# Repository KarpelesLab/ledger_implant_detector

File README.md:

# Ledger Implant Detector

> **⚠️ STATUS: CONCEPT — NOT YET BUILT OR VALIDATED (rev 0.1)**
>
> This hardware has **not been fabricated or tested yet**. The schematic,
> layout and detection method are a first-pass concept and will almost
> certainly need errata. Do not rely on this device to declare a wallet
> "clean" until the design has been built, characterised against known-good
> and known-tampered devices, and this banner has been removed.

A small hand-held tool for spotting **extra conductive structures hidden inside
the plastic shell of a hardware wallet** (e.g. a Ledger). The target threat is
a supply-chain implant that adds a cellular (LTE) modem to the device: such
implants need a comparatively large antenna, i.e. a sizeable area of copper
that is not present in a genuine unit.

Everything is on **one board**, powered and programmed over a single USB-C
port. No programmer or debug probe is needed (see
[Programming](#programming-no-tools-needed)).

## How it detects

The tool combines two complementary methods:

### 1. Capacitive electrode array (primary)

Eight 14 × 14 mm copper electrodes on the underside of the head are read by two
TI **FDC2214** 28-bit capacitance-to-digital converters (LC-resonant, EMI
tolerant). Any conductor close to a plate (an antenna trace, a ground plane, a
battery…) increases that plate's capacitance and lowers its resonance
frequency, which the FDC2214 measures with very high resolution.

The detector does **not** recognise an antenna by itself: a genuine wallet
also contains copper (PCB, battery, display, Bluetooth antenna, NFC coil on
newer models). The method is **differential**:

1. Lay a *known-genuine* unit of the same model on the head in a fixed
   orientation (a 3D-printed jig is recommended) and record the 8-channel
   signature (the "reference").
2. Lay the unit under test in the same position and compare.
3. A significant positive deviation localised to one or more electrodes means
   "more conductor here than in the reference" → open the device / investigate.

The array covers 65 × 34 mm, enough for a Nano S Plus / Nano X in a single
placement; Stax / Flex need two or more positions.

### 2. Near-field RF loop at the tip (secondary, needs a VNA)

The nose of the board carries a printed 8 mm H-field loop, fed by a 50 Ω
microstrip that runs back to an **edge SMA connector** next to the USB-C port.
Plug in an inexpensive VNA (NanoVNA / LiteVNA), sweep S11 from roughly
600 MHz to 3 GHz and hover the tip over the wallet. You are looking for
**resonances in the LTE bands** that a genuine unit does not show.

This is complementary to the capacitive method: capacitance tells you *where
there is extra copper*, and the RF sweep hints at *whether that copper is tuned
like an antenna*. Results are again comparative (reference unit vs. unit under
test). The wallet's own ground plane, battery, Bluetooth antenna and NFC coil
all produce responses of their own, and a hidden antenna's resonance shifts
with its surroundings.

A later revision is meant to integrate the RF sweep so no external VNA is
needed. The measurements in [docs/rf_measurements.md](docs/rf_measurements.md)
will decide whether a magnitude-only front end is enough or phase is needed.

## Simulations

[docs/simulation.md](docs/simulation.md) models the real antenna (from photos of
a tampered unit) sandwiched between the shell and the Ledger's own battery.
Summary so far: antenna copper that sticks out beyond the battery's outline is
clearly detectable, above any plausible placement error. Copper lying entirely
within the battery's outline (it is always glued between the shell and the
battery) and electrically floating is not detectable capacitively.
Placement (air gap) dominates the raw signal, so the wallet must be pressed flat
and judged by the *shape* of the 8-channel signature. The RF loop over the
antenna's feed area shows a narrow in-band absorption dip (~0.35 dB, at ~1.8 GHz
in the model) that a plain-copper piece of the same outline does not. That
feature tells an antenna apart from a battery or other metal, and is within
reach of a scalar, VNA-less front end.

The first NanoVNA session on a tampered Nano X
([data/rf/2026-10-18/notes.md](data/rf/2026-10-18/notes.md)) found a clear S21
hump at 820-850 MHz, but only with the probe right over the antenna's feed. To
remove that position dependence there is now a **concept RF fixture kit**
(slot line and open TEM cell, 80 × 80 mm test area, NanoVNA S11/S21), with
JLCPCB files. See [docs/fixtures.md](docs/fixtures.md). In simulation, both
fixtures see a narrow tampering notch at every wallet placement tested.

**First fixture measurements (2026-10-26, one genuine and one tampered Nano X,
[data/rf/2026-10-26/notes.md](data/rf/2026-10-26/notes.md)):** the TEM cell
shows a ~1 dB, ~40 MHz wide notch at 1171 MHz on the tampered unit in all 12
captures, at every placement and in both orientations. The simulation predicted
-1.2 dB at 1185 MHz. 18 of 19 genuine captures stay within 0.22 dB. One genuine
capture showed a similar notch at ~1230 MHz that did not repeat, cause unknown.
The slot line sees the antenna's 820-860 MHz resonance only weakly (~0.15 dB)
and only at 0 deg. This is promising but not yet validation: it is one unit of
each kind.

A second, quite different implant (Joe Grand's tampered Nano X: a hand-wound
~6 mm wire spiral antenna and a shortened battery) is **not** seen by the
fixtures in simulation: the coil is too small to couple to a uniform field. The
capacitive array catches it clearly through the missing battery foil
(1.3-3.4 pF above placement error). So always run both tests.

Two large crossed H-field loops (an induction-balance setup) were also
simulated ([docs/fixtures.md](docs/fixtures.md#large-loops-crossed-and-coaxial-simulation-only)).
Crossed vertical loops show the meander implant's 825-840 MHz resonance as a
10-13 dB narrow peak at every placement, but only 57-70 dB below the drive
level, which is hard for a NanoVNA. Wallet-sized coaxial loops miss that
resonance entirely. For now the TEM cell remains the practical test.

## Board

| Top | Bottom (sensing side) |
|---|---|
|  |  |

### Electrode map

Bottom copper, **seen from below** (i.e. the face you put against the wallet):

| Electrode | Converter | Channel |
|---|---|---|
| E1 / E5 / E6 / E2 | U1 (I²C 0x2A) | CH0 / CH1 / CH2 / CH3 |
| E3 / E7 / E8 / E4 | U2 (I²C 0x2B) | CH0 / CH1 / CH2 / CH3 |

Electrode numbering (E1…E4 = row nearest the RF edge, E1 nearest the nose) is
also printed on the bottom silkscreen.

### Stack-up

4 layers, 1.6 mm (JLC04161H-7628):

| Layer | Use |
|---|---|
| F.Cu | components, routing, GND pour, RF microstrip (0.35 mm ≈ 50 Ω over In1) |
| In1.Cu | solid GND: RF reference plane, and passive shield behind the electrodes so the hand holding the tool is not sensed |
| In2.Cu | routing **only outside the electrode areas** (keep-outs over every electrode); GND pour under the handle |
| B.Cu | the 8 electrodes (solder-mask covered); GND pour under the handle only |

Each FDC2214 sits on top of the board in the gap between its four electrodes,
so the sensor feed-throughs are only a few millimetres long.

### Parts

| Block | Part | Notes |
|---|---|---|
| CDC ×2 | TI FDC2214RGHR | single-ended sensors, 0x2A / 0x2B |
| Tank ×8 | 18 µH (Bourns CMH322522-180KL) ‖ 33 pF C0G 1 % | ≈ 5–6.5 MHz, values from the TI datasheet / EVM |
| Clock | 40 MHz CMOS oscillator (Abracon ASE) | shared by both FDCs |
| MCU | STM32F042F6P6 (TSSOP-20) | crystal-less USB FS, ROM USB-DFU bootloader |
| USB | USB-C (HRO TYPE-C-31-M-12), USBLC6-2SC6 ESD | 5.1 kΩ CC pull-downs (sink, 5 V only) |
| Power | AP2112K-3.3 LDO | |
| RF | printed 8 mm loop + Samtec SMA-J-P-H-ST-EM1 edge SMA | |
| UI | green + red LED, Murata PKLCS1212E piezo, CAL + BOOT buttons | |
| Expansion | JST-SH 4-pin (Qwiic / STEMMA-QT pinout) for an optional I²C OLED | |
| Debug | Tag-Connect TC2030-NL footprint (SWD), no part needed | |

### MCU pin map

| Pin | Function |
|---|---|
| PF0 / PF1 | I2C1 SDA / SCL (both FDCs + Qwiic) |
| PA0 / PA1 | FDC U1 / U2 INTB (10 k pull-ups) |
| PA2 | FDC SD (shutdown, both chips; 100 k pull-down = running) |
| PA3 / PA4 | LED green / red (active high) |
| PA5 | CAL button (to GND, enable internal pull-up) |
| PA6 | piezo buzzer (TIM3_CH1 / TIM16_CH1 PWM) |
| PA11 / PA12 | USB D− / D+ (TSSOP-20 pins 17/18, set `SYSCFG_CFGR1.PA11_PA12_RMP`) |
| PA13 / PA14 | SWDIO / SWCLK (Tag-Connect pads) |
| BOOT0 | BOOT button to 3V3 (10 k pull-down) |

## Programming (no tools needed)

The STM32F042 has a USB-DFU bootloader in ROM, so firmware is flashed through
the same USB-C port that powers the board:

- **Fresh board:** an unprogrammed STM32F04x starts straight into the ROM DFU
  bootloader (this is how projects such as
  [dap42](https://github.com/devanlai/dap42) are flashed).
- **Later:** hold **BOOT** while plugging in USB (or have the firmware jump to
  the bootloader on a USB command), then:

```sh
dfu-util -a 0 -s 0x08000000:leave -D firmware.bin
```

STM32CubeProgrammer (USB mode) works too. The Tag-Connect SWD footprint is
only there as a recovery/debug path for people who own a probe.

> To validate on the first build: that ROM DFU enumerates on the TSSOP-20 package
> (USB on the remapped pins 17/18), and the option-byte state of the BOOT0 pin on
> the delivered parts.

## Suggested FDC2214 configuration

Starting point, from datasheet §8.2.3:

- `CLOCK_DIVIDERS_CHx = 0x2001` (`CHx_FIN_SEL = b10`, single-ended sensor; `CHx_FREF_DIVIDER = 1`)
- External 40 MHz clock: `CONFIG.REF_CLK_SRC = 1`
- Tune `DRIVE_CURRENT_CHx` so the tank amplitude is 1.2–1.8 Vpk (start around IDRIVE = 15)
- Autoscan all 4 channels: `MUX_CONFIG.AUTOSCAN_EN = 1`, `RR_SEQUENCE = b10`, deglitch 10 MHz

## Repository layout

```
hardware/
  lib/                  project symbols + footprints (FDC2214, electrode, near-field loop)
  detector/             KiCad 10 project (schematic + 4-layer PCB)
    fab/                gerbers + drill (zip), BOM, JLC BOM/CPL, schematic PDF
docs/img/               renders
tools/                  Python generators used to produce the KiCad files and outputs
```

The KiCad files were generated by the scripts in `tools/` so the first
revision is reviewable as code. They are ordinary KiCad projects, though: once
you edit them by hand in KiCad, treat the KiCad files as the source of truth.

Regenerating needs KiCad 10 (its Python `pcbnew` module and `kicad-cli`). Routing also
needs Java 17+ and [Freerouting](https://github.com/freerouting/freerouting) **1.9.0**.
1.9 routes this board completely; 2.x did noticeably worse on it. 1.9 needs an X
display, and `Xvfb` works.

```sh
python3 tools/gen_lib.py              # project library
python3 tools/gen_detector_sch.py     # schematic
Xvfb :97 & export DISPLAY=:97
FREEROUTING_JAR=/path/to/freerouting-1.9.0.jar FREEROUTING_PASSES=100 \
    python3 tools/gen_detector_pcb.py # placement, pre-routing, autoroute, pours, stitching
python3 tools/make_outputs.py         # gerbers/drill/BOM/CPL/PDF + renders
```

The PCB generator places everything, then hand-routes these parts deterministically:
the RF microstrip, the converters' digital escapes, the north-side power/control
escapes, the tank for the electrode diagonally opposite each converter's analog pins,
and a small bus to the handle. It fans every GND pad out to the In1 plane and lets
Freerouting do the rest. GND is not autorouted: it comes from pours on F.Cu / In1 (and
In2 / B.Cu under the handle) plus stitching vias.

Current check status (`hardware/detector/fab/*_report.txt`): ERC 0 violations;
DRC 0 errors, 0 unconnected, schematic parity OK. The remaining warnings are two
"silkscreen clipped by board edge" from the stock USB-C footprint and three
single-spoke thermal reliefs on pads that also have a direct via to the GND plane.

## Ordering

`hardware/detector/fab/` contains everything for a 4-layer PCB + assembly
order:

- `implant_detector_gerbers.zip`: select 4 layers, 1.6 mm, and the
  **JLC04161H-7628** stack-up (the 0.35 mm RF line is 50 Ω only on that stack-up).
  Minimum features: 0.15 mm track/space, 0.3 mm drill / 0.6 mm via, so no
  advanced-capability options are needed.
- `bom_jlc.csv` + `cpl_jlc.csv` (origin = bottom-left corner of the board).
  MPNs are given; only the USB-C connector has a pre-filled LCSC number, so
  let the assembler match the rest by MPN and **check the rotations in the
  assembly preview**, especially U1/U2/U3, the LEDs and J1.
- The edge-launch SMA (J4) straddles the board edge. If the assembler won't
  place it, it is easy to hand-solder.
- The electrodes, the RF loop and the Tag-Connect footprint are bare copper,
  not parts.
- `schematic.pdf` for reference.

## Open questions the first build must answer

- [ ] Actual sensitivity through 1–3 mm of ABS/PC to a thin flex-PCB antenna.
- [ ] Repeatability between placements (jig needed?) and drift with temperature / hand proximity.
- [ ] Whether the solid In1 GND shield behind the electrodes costs too much range
      (alternatives: hatched shield, active shield driver).
- [ ] Electrode size / pitch trade-off (resolution vs. range).
- [ ] RF loop: usable frequency range and repeatability with NanoVNA-class instruments, and
      what an on-board (VNA-less) front end would need. See
      [docs/rf_measurements.md](docs/rf_measurements.md) and `tools/analyze_s1p.py`.
- [ ] ROM DFU on the TSSOP-20 STM32F042 (see above).
- [ ] Reference signatures for each Ledger model.

## License

Not yet chosen.

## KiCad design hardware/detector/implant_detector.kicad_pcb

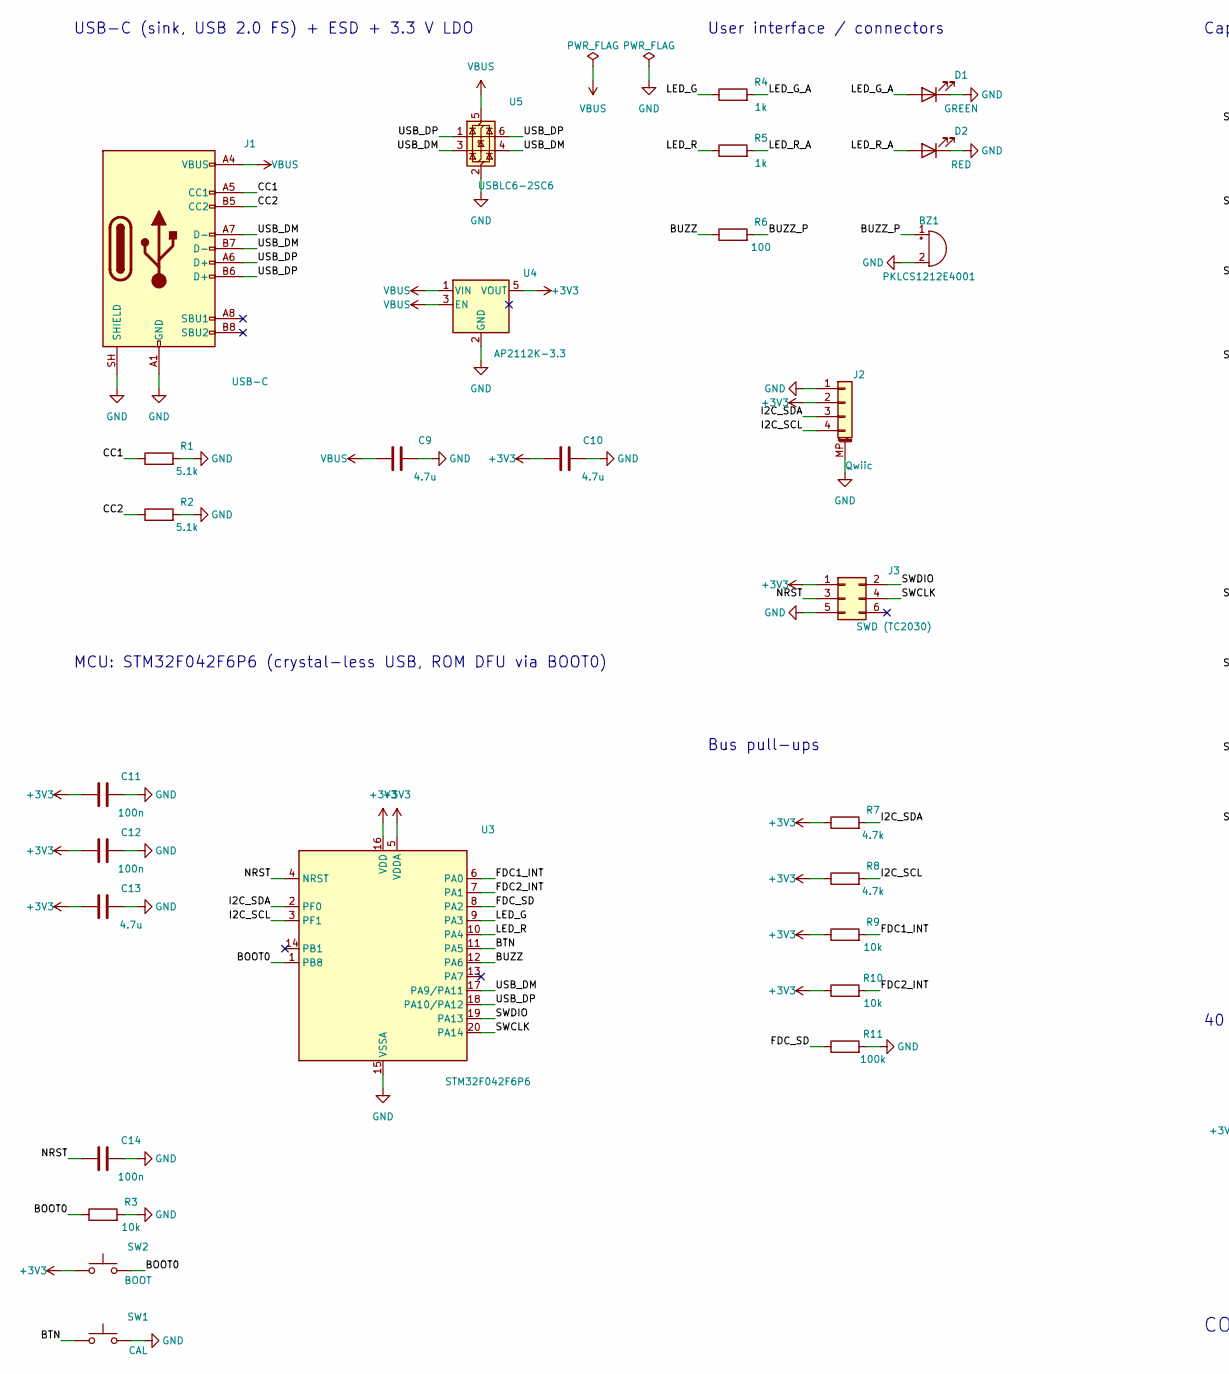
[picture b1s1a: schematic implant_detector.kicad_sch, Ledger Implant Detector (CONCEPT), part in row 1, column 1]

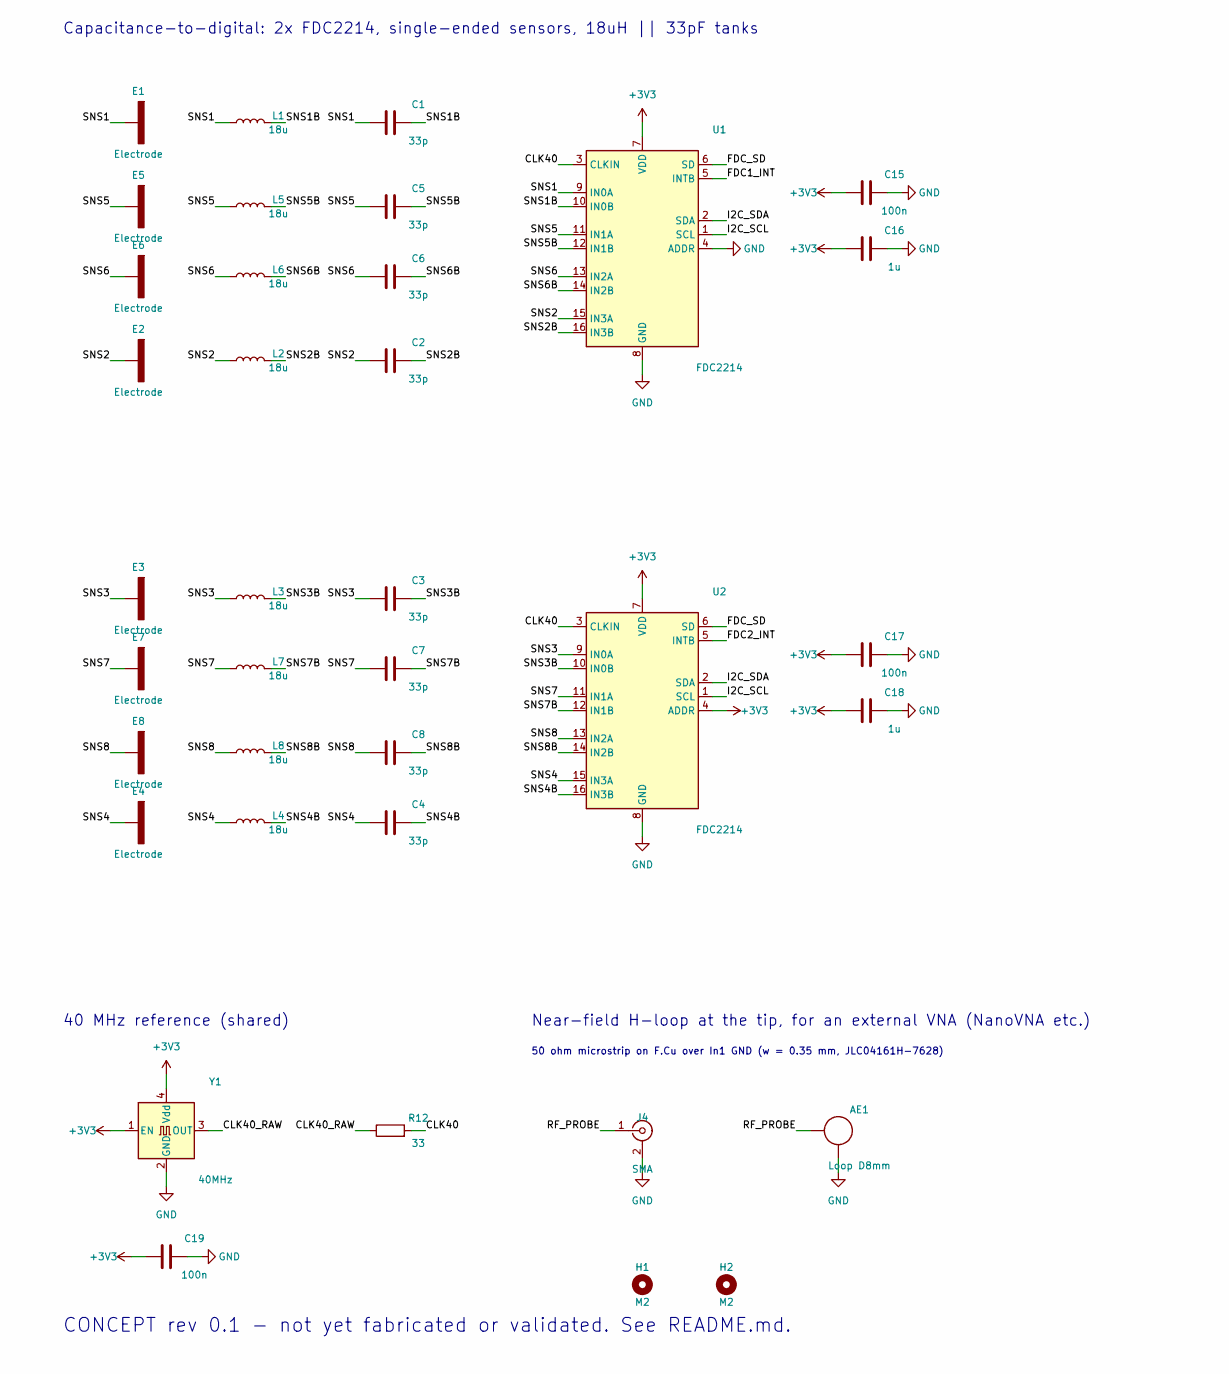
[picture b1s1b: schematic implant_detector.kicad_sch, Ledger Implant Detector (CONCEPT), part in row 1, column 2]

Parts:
AE1: Loop D8mm; NearField_Loop_D8mm
BZ1: PKLCS1212E4001; Buzzer_Murata_PKLCS1212E; MPN PKLCS1212E4001-R1
C1, C2, C3, C4, C5, C6, C7, C8: 33p; C_0603_1608Metric; Tolerance 1%; MPN GRM1885C1H330FA01D
C9, C10, C13: 4.7u; C_0603_1608Metric; Voltage 10V
C11, C12, C14, C15, C17, C19: 100n; C_0603_1608Metric
C16, C18: 1u; C_0603_1608Metric
D1: GREEN; LED_0603_1608Metric; MPN 19-217/GHC-YR1S2/3T
D2: RED; LED_0603_1608Metric; MPN 19-217/R6C-AL1M2VY/3T
E1, E2, E3, E4, E5, E6, E7, E8: Electrode; Electrode_14x14mm
H1, H2: M2; MountingHole_2.2mm_M2
J1: USB-C; USB_C_Receptacle_HRO_TYPE-C-31-M-12; MPN TYPE-C-31-M-12; LCSC C165948
J2: Qwiic; JST_SH_SM04B-SRSS-TB_1x04-1MP_P1.00mm_Horizontal; MPN SM04B-SRSS-TB(LF)(SN)
J3: SWD (TC2030); Tag-Connect_TC2030-IDC-NL_2x03_P1.27mm_Vertical
J4: SMA; SMA_Samtec_SMA-J-P-H-ST-EM1_EdgeMount; MPN SMA-J-P-H-ST-EM1
L1, L2, L3, L4, L5, L6, L7, L8: 18u; L_1210_3225Metric; MPN CMH322522-180KL
R1, R2: 5.1k; R_0603_1608Metric
R3, R9, R10: 10k; R_0603_1608Metric
R4, R5: 1k; R_0603_1608Metric
R6: 100; R_0603_1608Metric
R7, R8: 4.7k; R_0603_1608Metric
R11: 100k; R_0603_1608Metric
R12: 33; R_0603_1608Metric
SW1: CAL; SW_SPST_PTS810; MPN PTS810 SJM 250 SMTR LFS
SW2: BOOT; SW_SPST_PTS810; MPN PTS810 SJM 250 SMTR LFS
U1, U2: FDC2214; WQFN-16-1EP_4x4mm_P0.5mm_EP2.6x2.6mm; MPN FDC2214RGHR
U3: STM32F042F6P6; TSSOP-20_4.4x6.5mm_P0.65mm; MPN STM32F042F6P6
U4: AP2112K-3.3; SOT-23-5; MPN AP2112K-3.3TRG1
U5: USBLC6-2SC6; SOT-23-6; MPN USBLC6-2SC6
Y1: 40MHz; Oscillator_SMD_Abracon_ASE-4Pin_3.2x2.5mm; MPN ASE-40.000MHZ-LC-T

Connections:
+3V3: C10.1, C11.1, C12.1, C13.1, C15.1, C16.1, C17.1, C18.1, C19.1, J2.2, J3.1, R7.1, R8.1, R9.1, R10.1, SW2.1, U1.7 (VDD), U2.4 (ADDR), U2.7 (VDD), U3.5 (VDDA), U3.16 (VDD), U4.5 (VOUT), Y1.1 (EN), Y1.4 (Vdd)
/BOOT0: R3.1, SW2.2, U3.1 (PB8)
/BTN: SW1.1, U3.11 (PA5)
/BUZZ: R6.1, U3.12 (PA6)
/BUZZ_P: BZ1.1 (+), R6.2
/CC1: J1.A5 (CC1), R1.1
/CC2: J1.B5 (CC2), R2.1
/CLK40: R12.2, U1.3 (CLKIN), U2.3 (CLKIN)
/CLK40_RAW: R12.1, Y1.3 (OUT)
/FDC1_INT: R9.2, U1.5 (INTB), U3.6 (PA0)
/FDC2_INT: R10.2, U2.5 (INTB), U3.7 (PA1)
/FDC_SD: R11.1, U1.6 (SD), U2.6 (SD), U3.8 (PA2)
/I2C_SCL: J2.4, R8.2, U1.1 (SCL), U2.1 (SCL), U3.3 (PF1)
/I2C_SDA: J2.3, R7.2, U1.2 (SDA), U2.2 (SDA), U3.2 (PF0)
/LED_G: R4.1, U3.9 (PA3)
/LED_G_A: D1.2 (A), R4.2
/LED_R: R5.1, U3.10 (PA4)
/LED_R_A: D2.2 (A), R5.2
/NRST: C14.1, J3.3, U3.4 (NRST)
/RF_PROBE: AE1.1 (FEED), J4.1 (In)
/SNS1: C1.1, E1.1, L1.1, U1.9 (IN0A)
/SNS1B: C1.2, L1.2, U1.10 (IN0B)
/SNS2: C2.1, E2.1, L2.1, U1.15 (IN3A)
/SNS2B: C2.2, L2.2, U1.16 (IN3B)
/SNS3: C3.1, E3.1, L3.1, U2.9 (IN0A)
/SNS3B: C3.2, L3.2, U2.10 (IN0B)
/SNS4: C4.1, E4.1, L4.1, U2.15 (IN3A)
/SNS4B: C4.2, L4.2, U2.16 (IN3B)
/SNS5: C5.1, E5.1, L5.1, U1.11 (IN1A)
/SNS5B: C5.2, L5.2, U1.12 (IN1B)
/SNS6: C6.1, E6.1, L6.1, U1.13 (IN2A)
/SNS6B: C6.2, L6.2, U1.14 (IN2B)
/SNS7: C7.1, E7.1, L7.1, U2.11 (IN1A)
/SNS7B: C7.2, L7.2, U2.12 (IN1B)
/SNS8: C8.1, E8.1, L8.1, U2.13 (IN2A)
/SNS8B: C8.2, L8.2, U2.14 (IN2B)
/SWCLK: J3.4, U3.20 (PA14)
/SWDIO: J3.2, U3.19 (PA13)
/USB_DM: J1.A7 (D-), J1.B7 (D-), U3.17 (PA9/PA11), U5.3 (I/O2), U5.4 (I/O2)
/USB_DP: J1.A6 (D+), J1.B6 (D+), U3.18 (PA10/PA12), U5.1 (I/O1), U5.6 (I/O1)

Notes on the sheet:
USB-C (sink, USB 2.0 FS) + ESD + 3.3 V LDO
MCU: STM32F042F6P6 (crystal-less USB, ROM DFU via BOOT0)
User interface / connectors
Bus pull-ups
40 MHz reference (shared)
Capacitance-to-digital: 2x FDC2214, single-ended sensors, 18uH || 33pF tanks
Near-field H-loop at the tip, for an external VNA (NanoVNA etc.)
50 ohm microstrip on F.Cu over In1 GND (w = 0.35 mm, JLC04161H-7628)
CONCEPT rev 0.1 - not yet fabricated or validated. See README.md.

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
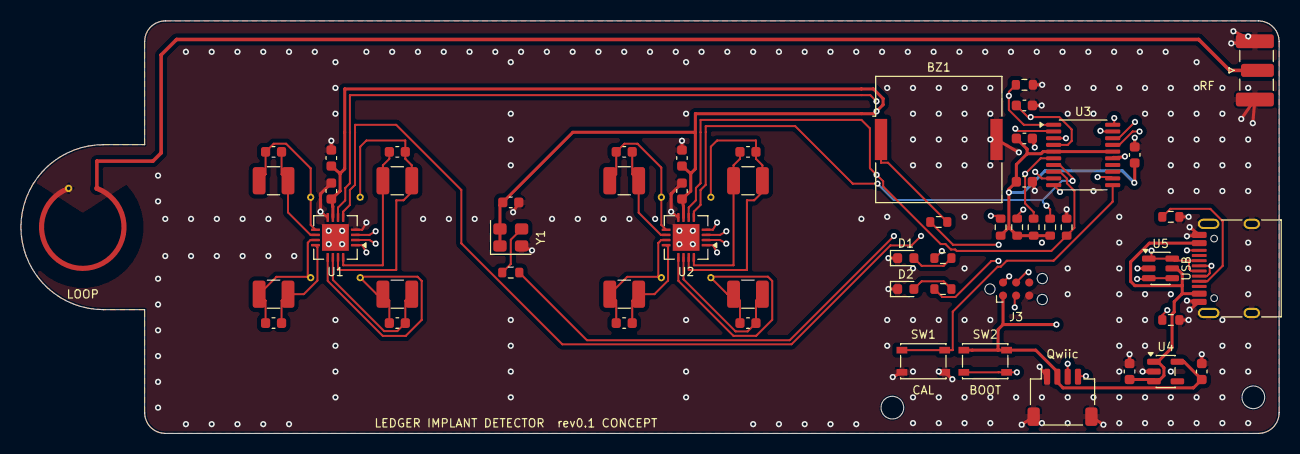
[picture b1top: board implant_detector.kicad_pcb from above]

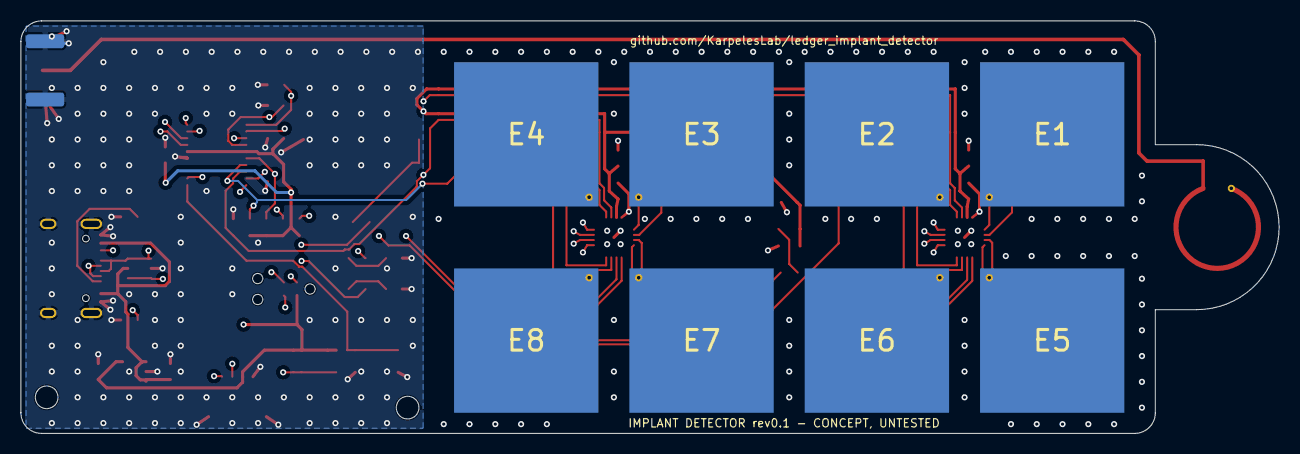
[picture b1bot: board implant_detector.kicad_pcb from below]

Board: 4 copper layers, 122.0 x 40.0 mm, 65 parts (8 on the bottom side), 42 nets.

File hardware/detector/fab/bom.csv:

"Designator","Value","Footprint","MPN","Manufacturer","LCSC","Qty","DNP"
"BZ1","PKLCS1212E4001","Buzzer_Beeper:Buzzer_Murata_PKLCS1212E","PKLCS1212E4001-R1","Murata","","1",""
"C1-C8","33p","Capacitor_SMD:C_0603_1608Metric","GRM1885C1H330FA01D","Murata","","8",""
"C9,C10,C13","4.7u","Capacitor_SMD:C_0603_1608Metric","","","","3",""
"C11,C12,C14,C15,C17,C19","100n","Capacitor_SMD:C_0603_1608Metric","","","","6",""
"C16,C18","1u","Capacitor_SMD:C_0603_1608Metric","","","","2",""
"D1","GREEN","LED_SMD:LED_0603_1608Metric","19-217/GHC-YR1S2/3T","Everlight","","1",""
"D2","RED","LED_SMD:LED_0603_1608Metric","19-217/R6C-AL1M2VY/3T","Everlight","","1",""
"J1","USB-C","Connector_USB:USB_C_Receptacle_HRO_TYPE-C-31-M-12","TYPE-C-31-M-12","Korean Hroparts Elec","C165948","1",""
"J2","Qwiic","Connector_JST:JST_SH_SM04B-SRSS-TB_1x04-1MP_P1.00mm_Horizontal","SM04B-SRSS-TB(LF)(SN)","JST","","1",""
"J4","SMA","Connector_Coaxial:SMA_Samtec_SMA-J-P-H-ST-EM1_EdgeMount","SMA-J-P-H-ST-EM1","Samtec","","1",""
"L1-L8","18u","Inductor_SMD:L_1210_3225Metric","CMH322522-180KL","Bourns","","8",""
"R1,R2","5.1k","Resistor_SMD:R_0603_1608Metric","","","","2",""
"R3,R9,R10","10k","Resistor_SMD:R_0603_1608Metric","","","","3",""
"R4,R5","1k","Resistor_SMD:R_0603_1608Metric","","","","2",""
"R6","100","Resistor_SMD:R_0603_1608Metric","","","","1",""
"R7,R8","4.7k","Resistor_SMD:R_0603_1608Metric","","","","2",""
"R11","100k","Resistor_SMD:R_0603_1608Metric","","","","1",""
"R12","33","Resistor_SMD:R_0603_1608Metric","","","","1",""
"SW1","CAL","Button_Switch_SMD:SW_SPST_PTS810","PTS810 SJM 250 SMTR LFS","C&K","","1",""
"SW2","BOOT","Button_Switch_SMD:SW_SPST_PTS810","PTS810 SJM 250 SMTR LFS","C&K","","1",""
"U1,U2","FDC2214","Package_DFN_QFN:WQFN-16-1EP_4x4mm_P0.5mm_EP2.6x2.6mm","FDC2214RGHR","Texas Instruments","","2",""
"U3","STM32F042F6P6","Package_SO:TSSOP-20_4.4x6.5mm_P0.65mm","STM32F042F6P6","STMicroelectronics","","1",""
"U4","AP2112K-3.3","Package_TO_SOT_SMD:SOT-23-5","AP2112K-3.3TRG1","Diodes Inc","","1",""
"U5","USBLC6-2SC6","Package_TO_SOT_SMD:SOT-23-6","USBLC6-2SC6","STMicroelectronics","","1",""
"Y1","40MHz","Oscillator:Oscillator_SMD_Abracon_ASE-4Pin_3.2x2.5mm","ASE-40.000MHZ-LC-T","Abracon","","1",""

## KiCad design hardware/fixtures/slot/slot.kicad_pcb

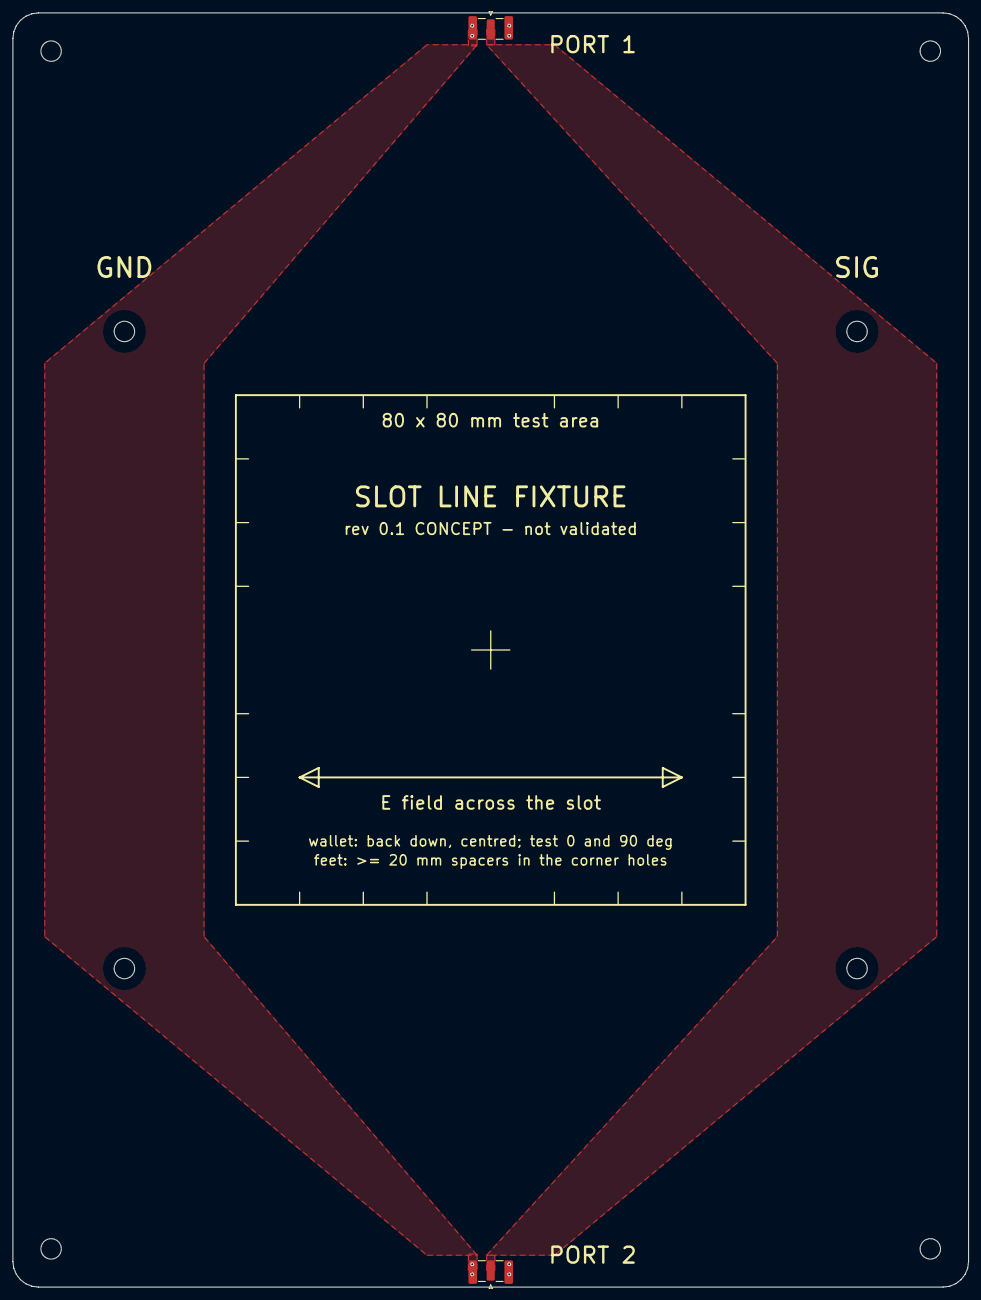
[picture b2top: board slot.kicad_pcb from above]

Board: 2 copper layers, 150.0 x 200.0 mm, 10 parts (0 on the bottom side), 2 nets, no tracks yet.

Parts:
H1, H2, H3, H4, H5, H6, H7, H8: MountingHole_3.2mm_M3
J1, J2: SMA edge jack (Samtec SMA-J-P-H-ST-EM1); SMA_Samtec_SMA-J-P-H-ST-EM1_EdgeMount

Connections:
GND: J1.2, J2.2
SIG: J1.1, J2.1

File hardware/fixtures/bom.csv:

Item,Qty per kit,Used on,Designators,Description,Suggested part,Notes
1,4,slot (2) + tem_base (2),J1 J2,"SMA female jack, edge mount / end launch, for 1.6 mm PCB, 50 ohm","Samtec SMA-J-P-H-ST-EM1 (footprint used); generic 'SMA-KE 1.6 mm' edge jacks also fit (e.g. Adafruit 1865)",Hand-soldered: centre pin + 2 legs top + 2 legs bottom
2,4,carrier,H1-H4,"M3 nylon hex spacer, female-female, 5 / 10 / 15 / 20 mm (one set of 4 per height you want to test)",any,Nylon only near the test area
3,4,tem_base + tem_plate,H1-H4,"M3 nylon hex spacer, female-female, 15 / 20 / 25 / 30 mm (one set of 4 per cell height h)",any,20 mm = 50 ohm cell
4,8,slot + tem_base,H5-H8,"M3 nylon spacer >= 20 mm, used as feet",any,
5,24,all,,M3 x 6 nylon screw,any,
6,1,tem_plate + 2 x tem_ramp,,"Conductive copper foil tape, 5-10 mm wide (conductive adhesive)",any,Ramp-to-septum joints; tack-solder
7,1,either fixture,,"SMA 50 ohm termination, male",any (the NanoVNA calibration load works),Only for S11-only tests
